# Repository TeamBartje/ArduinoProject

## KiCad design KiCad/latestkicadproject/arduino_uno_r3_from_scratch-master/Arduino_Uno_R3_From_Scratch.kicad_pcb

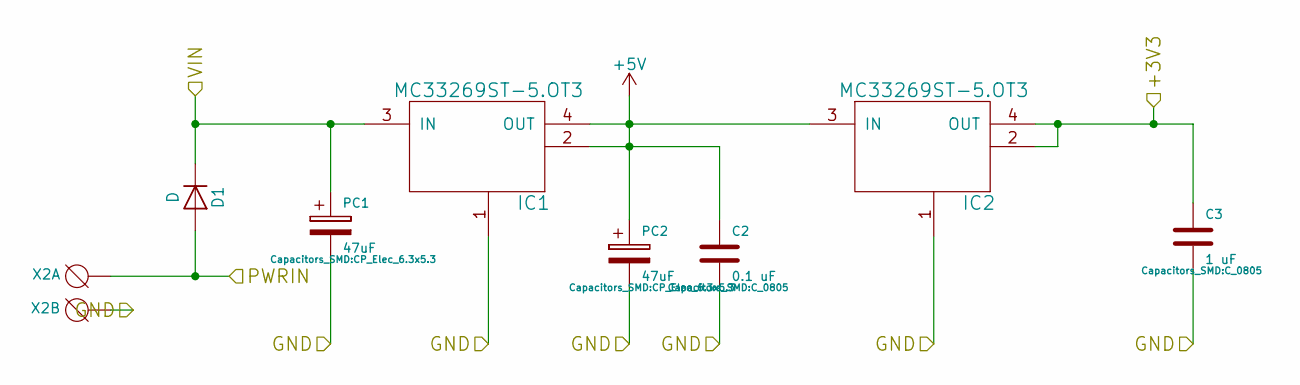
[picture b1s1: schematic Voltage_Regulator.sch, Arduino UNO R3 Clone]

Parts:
C2: 0.1 uF; C_0805
C3: 1 uF; C_0805
D1: D; D_MiniMELF_Handsoldering
IC1, IC2: MC33269ST-5.OT3; SOT230P700X175-4N
PC1, PC2: 47uF; CP_Elec_6.3x5.3
X2: DG3XX-02-3.5; degson-DG350-3.5-02P

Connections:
+5V: C2.1, IC1.2, IC1.4 (OUT), IC2.3 (IN), PC2.1; also elsewhere on the board
/Headers/+3V3: C3.1, IC2.2, IC2.4 (OUT); also elsewhere on the board
/Headers/VIN: D1.1 (K), IC1.3 (IN), PC1.1; also elsewhere on the board
/Motor Outputs/PWRIN: D1.2 (A), X2.1; also elsewhere on the board
GND: C2.2, C3.2, IC1.1, IC2.1, PC1.2, PC2.2, X2.2; also elsewhere on the board

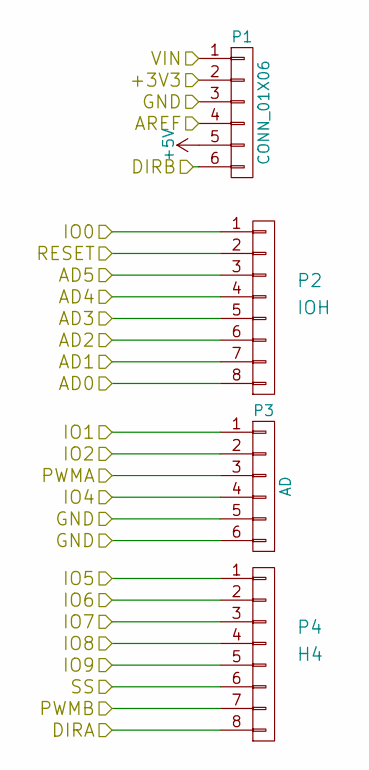
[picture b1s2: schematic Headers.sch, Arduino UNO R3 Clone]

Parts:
P1: CONN_01X06; Pin_Header_Straight_1x06_Pitch2.54mm
P2: IOH; Pin_Header_Straight_1x08_Pitch2.54mm
P3: AD; Pin_Header_Straight_1x06_Pitch2.54mm
P4: H4; Pin_Header_Straight_1x08_Pitch2.54mm

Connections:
+5V: P1.5; also elsewhere on the board
/ATMEGA328P/AD0: P2.8; also elsewhere on the board
/ATMEGA328P/AD1: P2.7; also elsewhere on the board
/ATMEGA328P/AD2: P2.6; also elsewhere on the board
/ATMEGA328P/AD3: P2.5; also elsewhere on the board
/ATMEGA328P/AD4: P2.4; also elsewhere on the board
/ATMEGA328P/AD5: P2.3; also elsewhere on the board
/ATMEGA328P/AREF: P1.4; also elsewhere on the board
/ATMEGA328P/DIRA: P4.8; also elsewhere on the board
/ATMEGA328P/DIRB: P1.6; also elsewhere on the board
/ATMEGA328P/IO0: P2.1; also elsewhere on the board
/ATMEGA328P/IO1: P3.1; also elsewhere on the board
/ATMEGA328P/IO2: P3.2; also elsewhere on the board
/ATMEGA328P/IO4: P3.4; also elsewhere on the board
/ATMEGA328P/IO5: P4.1; also elsewhere on the board
/ATMEGA328P/IO6: P4.2; also elsewhere on the board
/ATMEGA328P/IO7: P4.3; also elsewhere on the board
/ATMEGA328P/IO8: P4.4; also elsewhere on the board
/ATMEGA328P/IO9: P4.5; also elsewhere on the board
/ATMEGA328P/PWMA: P3.3; also elsewhere on the board
/ATMEGA328P/PWMB: P4.7; also elsewhere on the board
/ATMEGA328P/RESET: P2.2; also elsewhere on the board
/ATMEGA328P/SS: P4.6; also elsewhere on the board
/Headers/+3V3: P1.2; also elsewhere on the board
/Headers/VIN: P1.1; also elsewhere on the board
GND: P1.3, P3.5, P3.6; also elsewhere on the board

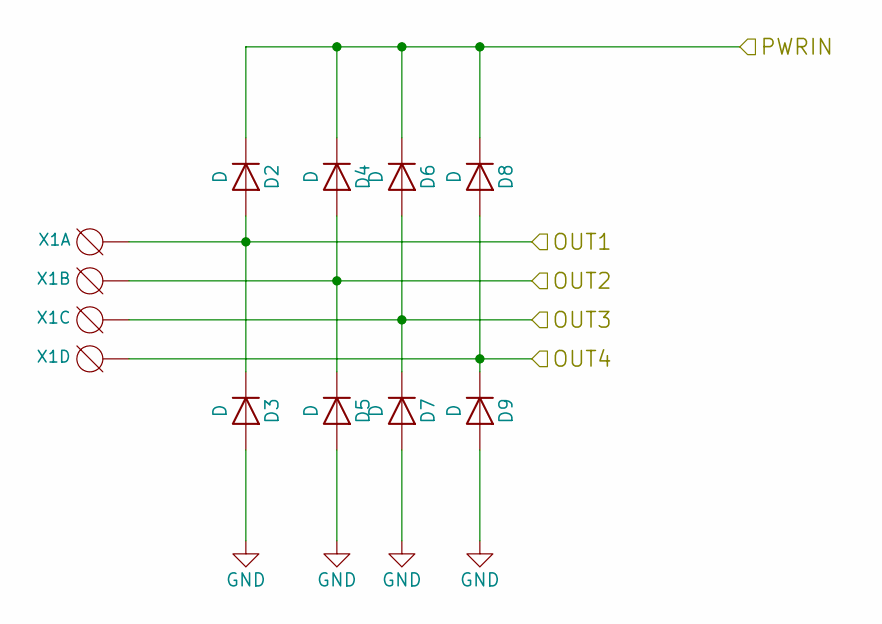
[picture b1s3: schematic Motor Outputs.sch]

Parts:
D2, D3, D4, D5, D6, D7, D8, D9: D; DIOM5437X240N
X1: DG3XX-04-3.5; degson-DG350-3.5-04P

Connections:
/Driver/OUT1: D2.2 (A), D3.1 (K), X1.1; also elsewhere on the board
/Driver/OUT2: D4.2 (A), D5.1 (K), X1.2; also elsewhere on the board
/Driver/OUT3: D6.2 (A), D7.1 (K), X1.3; also elsewhere on the board
/Driver/OUT4: D8.2 (A), D9.1 (K), X1.4; also elsewhere on the board
/Motor Outputs/PWRIN: D2.1 (K), D4.1 (K), D6.1 (K), D8.1 (K); also elsewhere on the board
GND: D3.2 (A), D5.2 (A), D7.2 (A), D9.2 (A); also elsewhere on the board

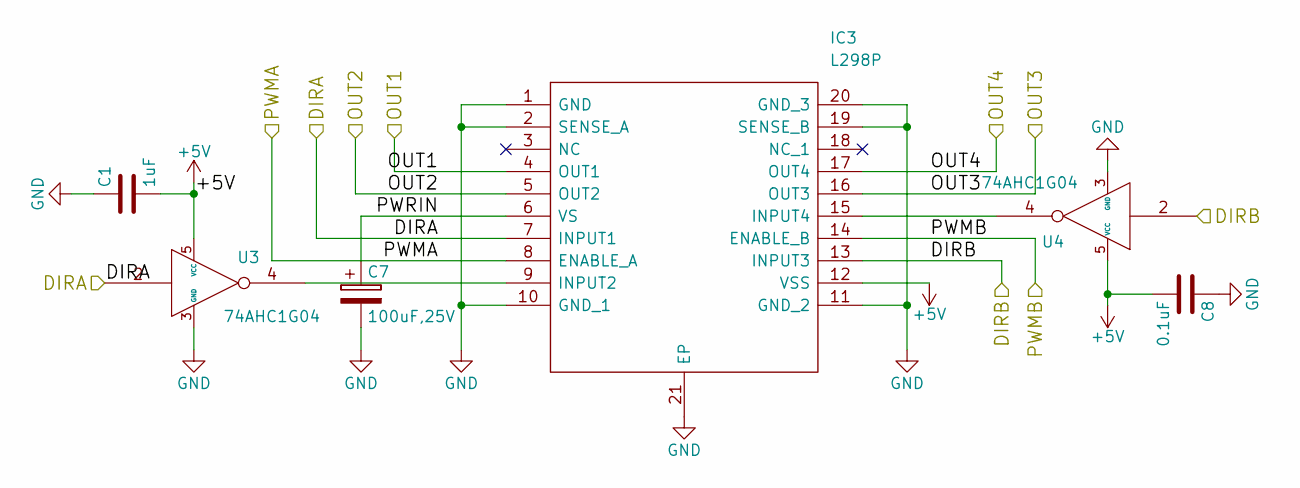
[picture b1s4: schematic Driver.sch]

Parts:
C1: 1uF; C_0805
C7: 100uF,25V; CP_Elec_6.3x5.3
C8: 0.1uF; C_0805
IC3: L298P; SOIC127P1420X360-21N; Manufacturer_Part_Number L298P
U3, U4: 74AHC1G04; 74AHC1G04GW

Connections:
+5V: C1.2, C8.2, IC3.12 (VSS), U3.5 (VCC), U4.5 (VCC); also elsewhere on the board
/ATMEGA328P/DIRA: IC3.7 (INPUT1), U3.2; also elsewhere on the board
/ATMEGA328P/DIRB: IC3.13 (INPUT3), U4.2; also elsewhere on the board
/ATMEGA328P/PWMA: IC3.8 (ENABLE_A); also elsewhere on the board
/ATMEGA328P/PWMB: IC3.14 (ENABLE_B); also elsewhere on the board
/Driver/OUT1: IC3.4 (OUT1); also elsewhere on the board
/Driver/OUT2: IC3.5 (OUT2); also elsewhere on the board
/Driver/OUT3: IC3.16 (OUT3); also elsewhere on the board
/Driver/OUT4: IC3.17 (OUT4); also elsewhere on the board
/Driver/PWRIN: C7.1, IC3.6 (VS)
GND: C1.1, C7.2, C8.1, IC3.1 (GND), IC3.2 (SENSE_A), IC3.10 (GND_1), IC3.11 (GND_2), IC3.19 (SENSE_B), IC3.20 (GND_3), IC3.21 (EP), U3.3 (GND), U4.3 (GND); also elsewhere on the board
unnamed: IC3.9 (INPUT2), U3.4
unnamed: IC3.15 (INPUT4), U4.4

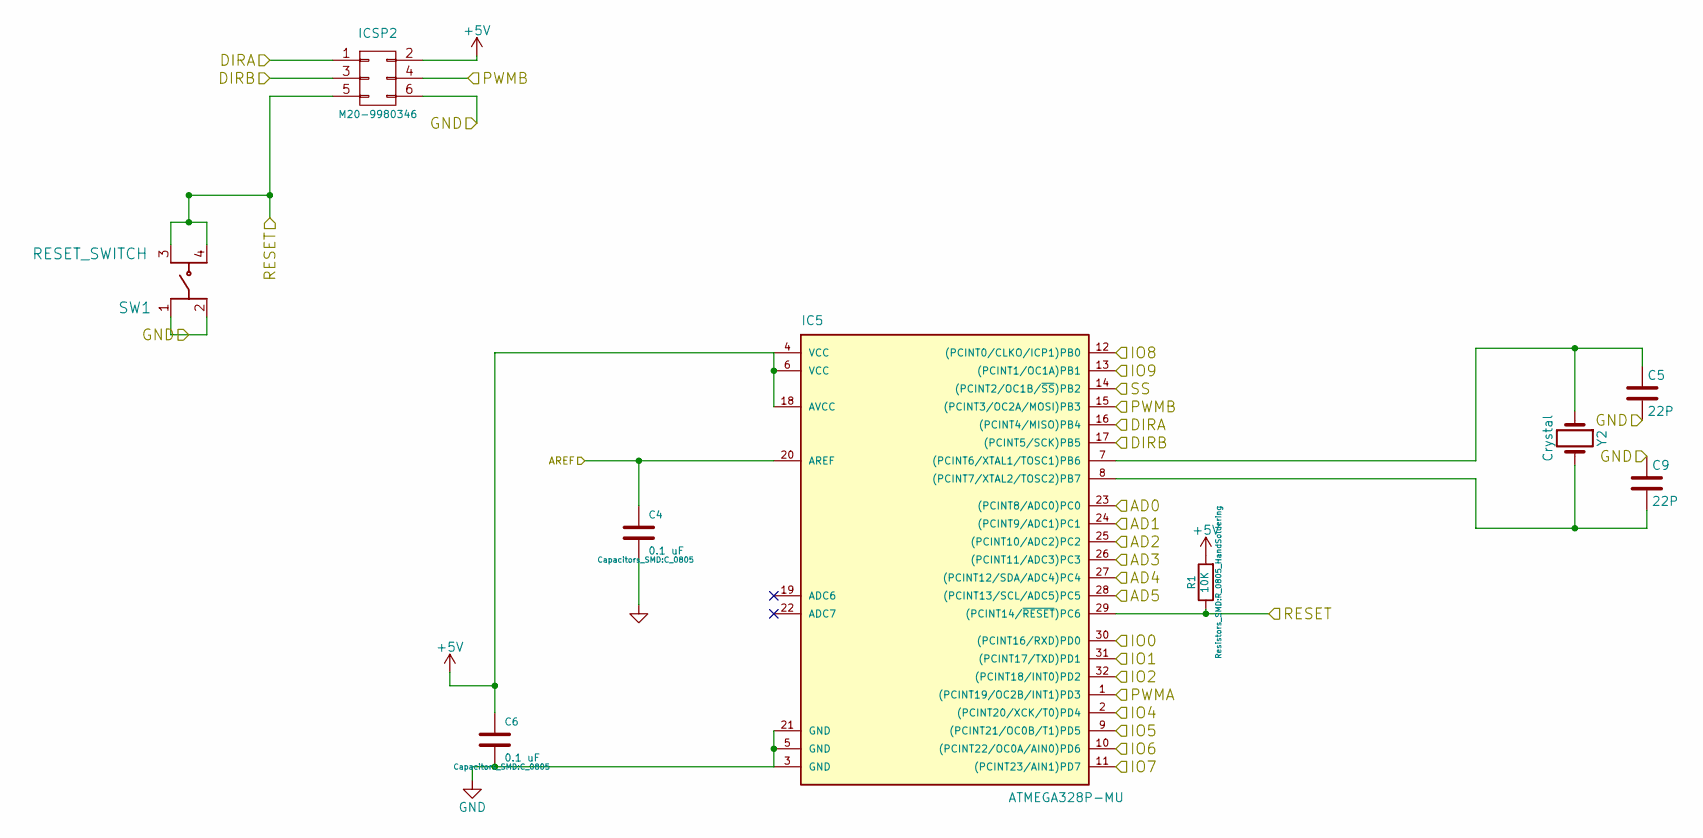
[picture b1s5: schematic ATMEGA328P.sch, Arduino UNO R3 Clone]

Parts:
C4, C6: 0.1 uF; C_0805
C5, C9: 22P; C_0805
IC5: ATMEGA328P-MU; QFP80P900X900X120-32N
ICSP2: M20-9980346; HDRV6W64P254_2X3_762X508X868P
R1: 10K; R_0805_HandSoldering
SW1: RESET_SWITCH; FSM4JSMATR
Y2: Crystal; HC%2f49US-(AT49)_1

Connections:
+5V: C6.1, IC5.4 (VCC), IC5.6 (VCC), IC5.18 (AVCC), ICSP2.2, R1.2; also elsewhere on the board
/ATMEGA328P/AD0: IC5.23 ((PCINT8/ADC0)PC0); also elsewhere on the board
/ATMEGA328P/AD1: IC5.24 ((PCINT9/ADC1)PC1); also elsewhere on the board
/ATMEGA328P/AD2: IC5.25 ((PCINT10/ADC2)PC2); also elsewhere on the board
/ATMEGA328P/AD3: IC5.26 ((PCINT11/ADC3)PC3); also elsewhere on the board
/ATMEGA328P/AD4: IC5.27 ((PCINT12/SDA/ADC4)PC4); also elsewhere on the board
/ATMEGA328P/AD5: IC5.28 ((PCINT13/SCL/ADC5)PC5); also elsewhere on the board
/ATMEGA328P/AREF: C4.1, IC5.20 (AREF); also elsewhere on the board
/ATMEGA328P/DIRA: IC5.16 ((PCINT4/MISO)PB4), ICSP2.1; also elsewhere on the board
/ATMEGA328P/DIRB: IC5.17 ((PCINT5/SCK)PB5), ICSP2.3; also elsewhere on the board
/ATMEGA328P/IO0: IC5.30 ((PCINT16/RXD)PD0); also elsewhere on the board
/ATMEGA328P/IO1: IC5.31 ((PCINT17/TXD)PD1); also elsewhere on the board
/ATMEGA328P/IO2: IC5.32 ((PCINT18/INT0)PD2); also elsewhere on the board
/ATMEGA328P/IO4: IC5.2 ((PCINT20/XCK/T0)PD4); also elsewhere on the board
/ATMEGA328P/IO5: IC5.9 ((PCINT21/OC0B/T1)PD5); also elsewhere on the board
/ATMEGA328P/IO6: IC5.10 ((PCINT22/OC0A/AIN0)PD6); also elsewhere on the board
/ATMEGA328P/IO7: IC5.11 ((PCINT23/AIN1)PD7); also elsewhere on the board
/ATMEGA328P/IO8: IC5.12 ((PCINT0/CLKO/ICP1)PB0); also elsewhere on the board
/ATMEGA328P/IO9: IC5.13 ((PCINT1/OC1A)PB1); also elsewhere on the board
/ATMEGA328P/PWMA: IC5.1 ((PCINT19/OC2B/INT1)PD3); also elsewhere on the board
/ATMEGA328P/PWMB: IC5.15 ((PCINT3/OC2A/MOSI)PB3), ICSP2.4; also elsewhere on the board
/ATMEGA328P/RESET: IC5.29 ((PCINT14/~RESET~)PC6), ICSP2.5, R1.1, SW1.3, SW1.4; also elsewhere on the board
/ATMEGA328P/SS: IC5.14 ((PCINT2/OC1B/~SS~)PB2); also elsewhere on the board
GND: C4.2, C5.2, C6.2, C9.1, IC5.3 (GND), IC5.5 (GND), IC5.21 (GND), ICSP2.6, SW1.1, SW1.2; also elsewhere on the board
unnamed: C5.1, IC5.7 ((PCINT6/XTAL1/TOSC1)PB6), Y2.1
unnamed: C9.2, IC5.8 ((PCINT7/XTAL2/TOSC2)PB7), Y2.2

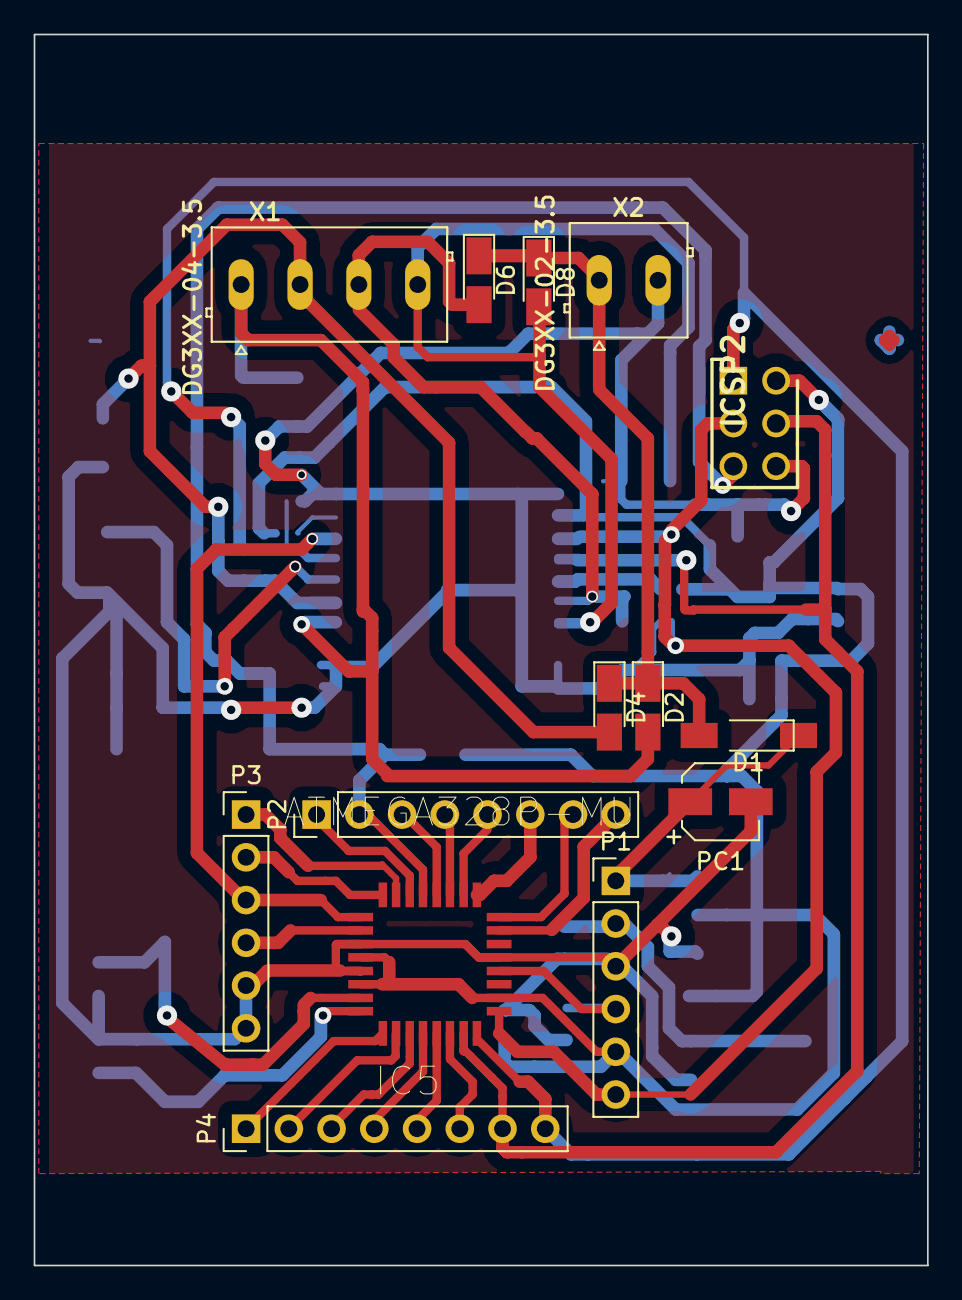
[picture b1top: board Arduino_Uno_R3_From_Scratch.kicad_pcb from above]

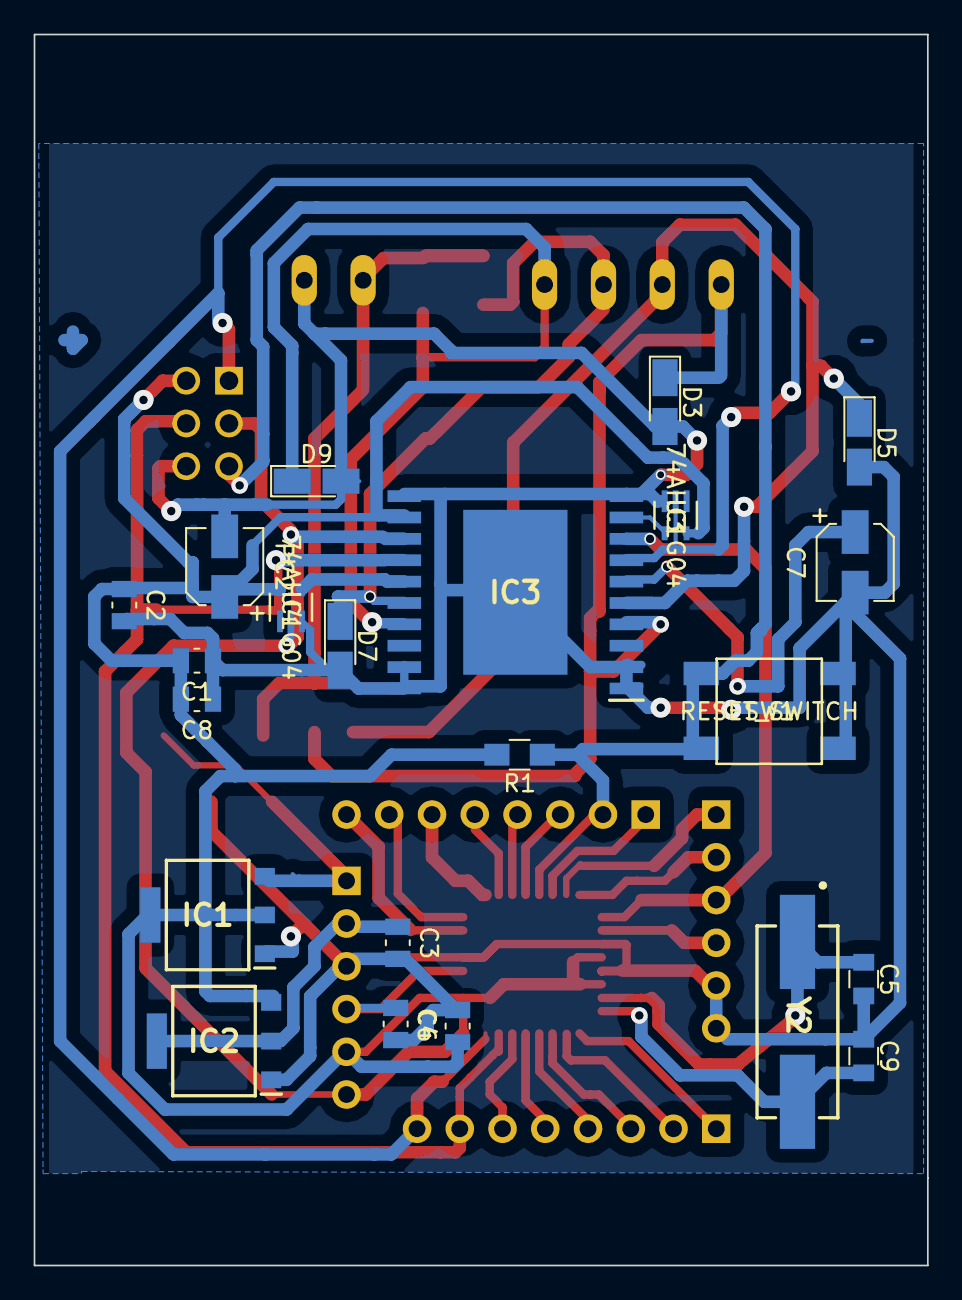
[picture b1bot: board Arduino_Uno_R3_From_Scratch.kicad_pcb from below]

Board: 2 copper layers, 53.1 x 73.2 mm, 36 parts (22 on the bottom side), 36 nets.

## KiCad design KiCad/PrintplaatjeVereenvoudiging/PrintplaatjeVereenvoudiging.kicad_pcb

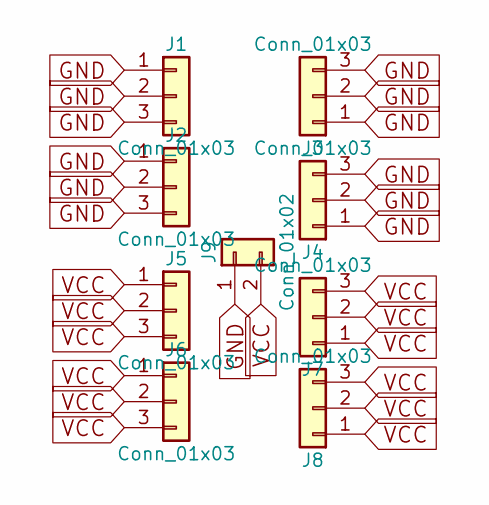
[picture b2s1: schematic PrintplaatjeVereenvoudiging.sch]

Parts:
J1, J2, J3, J4, J5, J6, J7, J8: Conn_01x03; Pin_Header_Angled_1x03_Pitch2.54mm
J9: Conn_01x02; Pin_Header_Angled_1x02_Pitch2.54mm

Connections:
GND: J1.1, J1.2, J1.3, J2.1, J2.2, J2.3, J3.1, J3.2, J3.3, J4.1, J4.2, J4.3, J9.1
VCC: J5.1, J5.2, J5.3, J6.1, J6.2, J6.3, J7.1, J7.2, J7.3, J8.1, J8.2, J8.3, J9.2

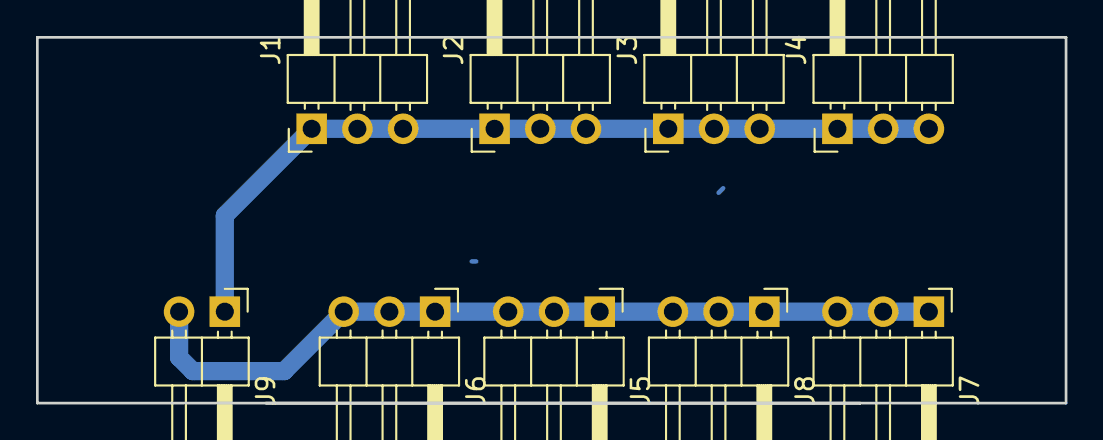
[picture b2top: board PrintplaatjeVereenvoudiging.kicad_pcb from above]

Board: 2 copper layers, 57.1 x 20.3 mm, 9 parts (0 on the bottom side), 2 nets.

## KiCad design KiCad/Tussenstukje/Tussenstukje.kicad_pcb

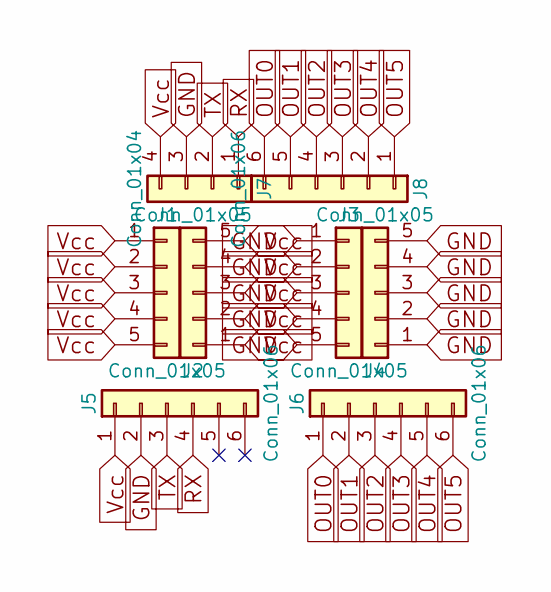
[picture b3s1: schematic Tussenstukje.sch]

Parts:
J1, J2, J3, J4: Conn_01x05; Pin_Header_Straight_1x05_Pitch2.54mm
J5, J6: Conn_01x06; Pin_Header_Straight_1x06_Pitch2.54mm
J7: Conn_01x04; Pin_Header_Angled_1x04_Pitch2.54mm
J8: Conn_01x06; Pin_Header_Angled_1x06_Pitch2.54mm

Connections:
GND: J3.1, J3.2, J3.3, J3.4, J3.5, J4.1, J4.2, J4.3, J4.4, J4.5, J5.2, J7.3
OUT0: J6.1, J8.6
OUT1: J6.2, J8.5
OUT2: J6.3, J8.4
OUT3: J6.4, J8.3
OUT4: J6.5, J8.2
OUT5: J6.6, J8.1
RX: J5.4, J7.1
TX: J5.3, J7.2
Vcc: J1.1, J1.2, J1.3, J1.4, J1.5, J2.1, J2.2, J2.3, J2.4, J2.5, J5.1, J7.4

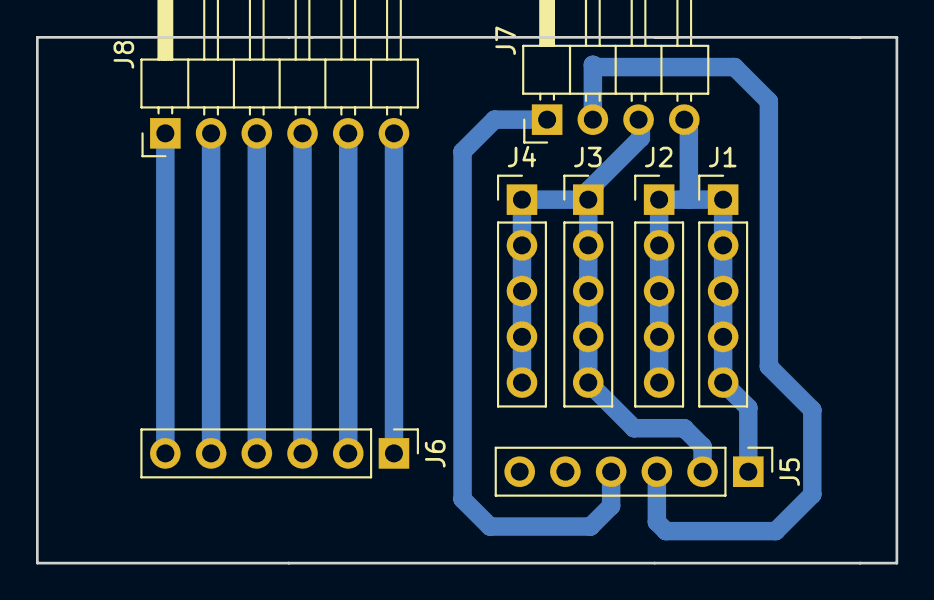
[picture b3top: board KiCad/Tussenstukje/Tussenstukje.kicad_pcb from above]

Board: 2 copper layers, 47.8 x 29.2 mm, 8 parts (0 on the bottom side), 10 nets.

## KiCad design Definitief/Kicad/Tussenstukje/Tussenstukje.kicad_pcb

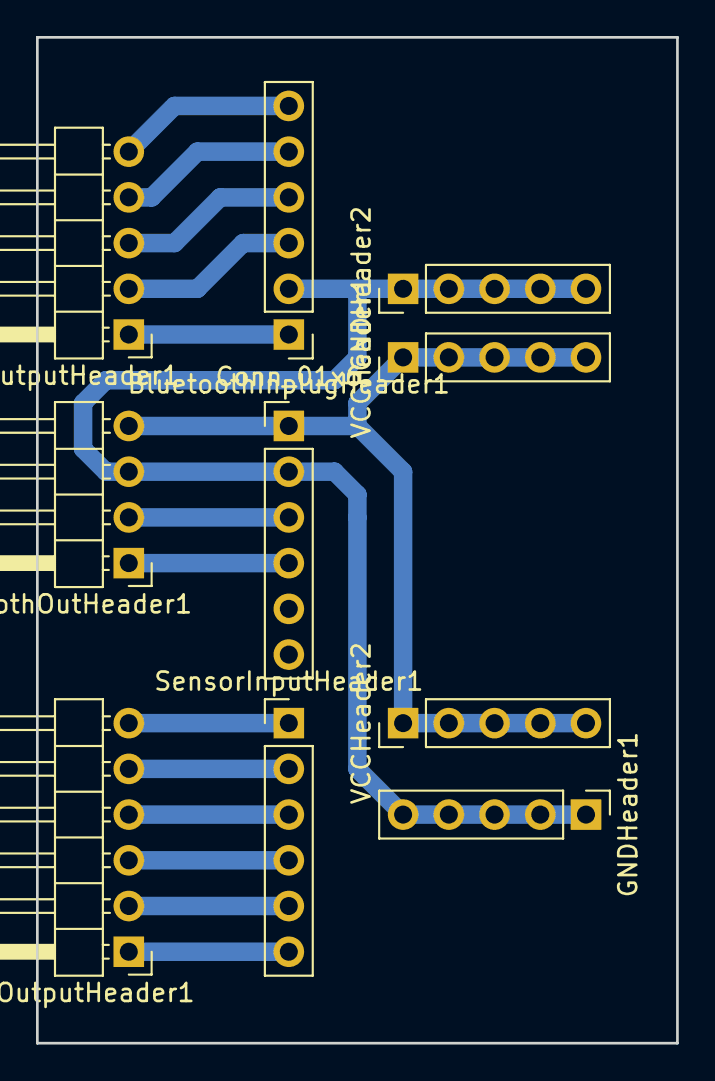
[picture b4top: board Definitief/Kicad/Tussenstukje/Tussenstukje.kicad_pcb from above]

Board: 2 copper layers, 35.6 x 55.9 mm, 10 parts (0 on the bottom side), 15 nets.

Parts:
BluetoothInplugHeader1: Conn_01x06; Pin_Header_Straight_1x06_Pitch2.54mm
BluetoothOutHeader1: BluetoothOutputHeader; Pin_Header_Angled_1x04_Pitch2.54mm
Conn_01x6: RFIDInplugHeader; Pin_Header_Straight_1x06_Pitch2.54mm
GNDHeader1: GNDHeader1; Pin_Header_Straight_1x05_Pitch2.54mm
GNDHeader2: GNDHeader2; Pin_Header_Straight_1x05_Pitch2.54mm
RFIDOutputHeader1: Conn_01x05; Pin_Header_Angled_1x05_Pitch2.54mm
SensorInputHeader1: SensorInputHeader; Pin_Header_Straight_1x06_Pitch2.54mm
SensorOutputHeader1: Conn_01x06; Pin_Header_Angled_1x06_Pitch2.54mm
VCCHeader1, VCCHeader2: Conn_01x05; Pin_Header_Straight_1x05_Pitch2.54mm

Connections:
GND: BluetoothInplugHeader1.2, BluetoothOutHeader1.3, Conn_01x6.2, GNDHeader1.1, GNDHeader1.2, GNDHeader1.3, GNDHeader1.4, GNDHeader1.5, GNDHeader2.1, GNDHeader2.2, GNDHeader2.3, GNDHeader2.4, GNDHeader2.5
MISO: Conn_01x6.3, RFIDOutputHeader1.2
MOSI: Conn_01x6.4, RFIDOutputHeader1.3
OUT0: SensorInputHeader1.6, SensorOutputHeader1.1
OUT1: SensorInputHeader1.5, SensorOutputHeader1.2
OUT2: SensorInputHeader1.4, SensorOutputHeader1.3
OUT3: SensorInputHeader1.3, SensorOutputHeader1.4
OUT4: SensorInputHeader1.2, SensorOutputHeader1.5
OUT5: SensorInputHeader1.1, SensorOutputHeader1.6
RX: BluetoothInplugHeader1.4, BluetoothOutHeader1.1
SCK: Conn_01x6.5, RFIDOutputHeader1.4
SDA: Conn_01x6.6, RFIDOutputHeader1.5
TX: BluetoothInplugHeader1.3, BluetoothOutHeader1.2
VCC3.3: Conn_01x6.1, RFIDOutputHeader1.1
Vcc: BluetoothInplugHeader1.1, BluetoothOutHeader1.4, VCCHeader1.1, VCCHeader1.2, VCCHeader1.3, VCCHeader1.4, VCCHeader1.5, VCCHeader2.1, VCCHeader2.2, VCCHeader2.3, VCCHeader2.4, VCCHeader2.5

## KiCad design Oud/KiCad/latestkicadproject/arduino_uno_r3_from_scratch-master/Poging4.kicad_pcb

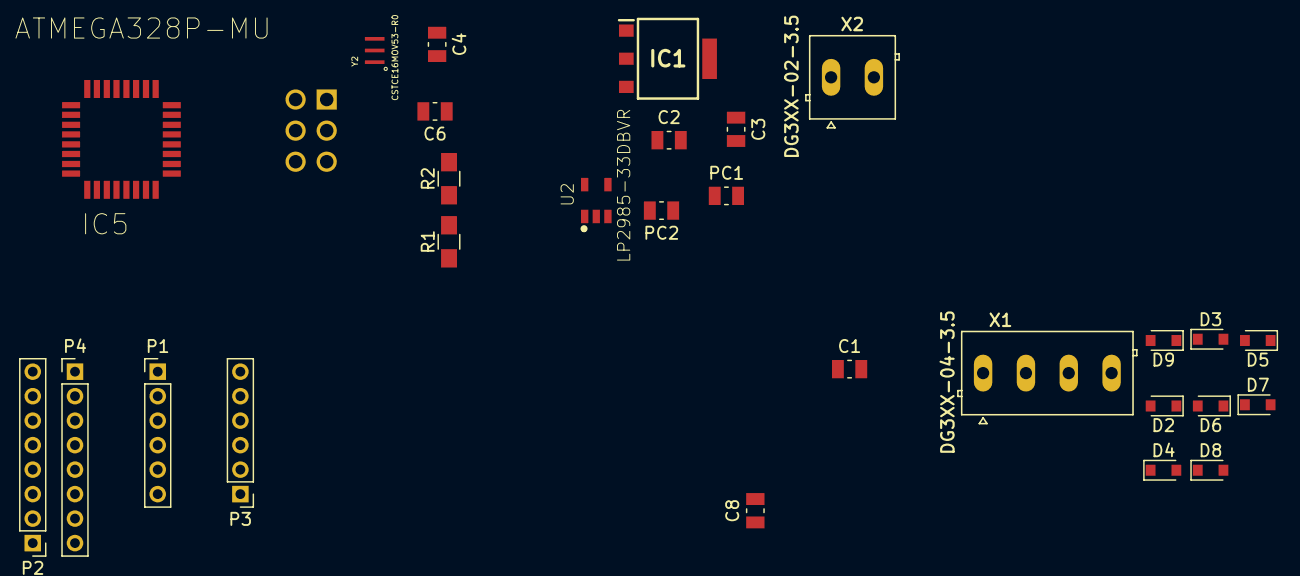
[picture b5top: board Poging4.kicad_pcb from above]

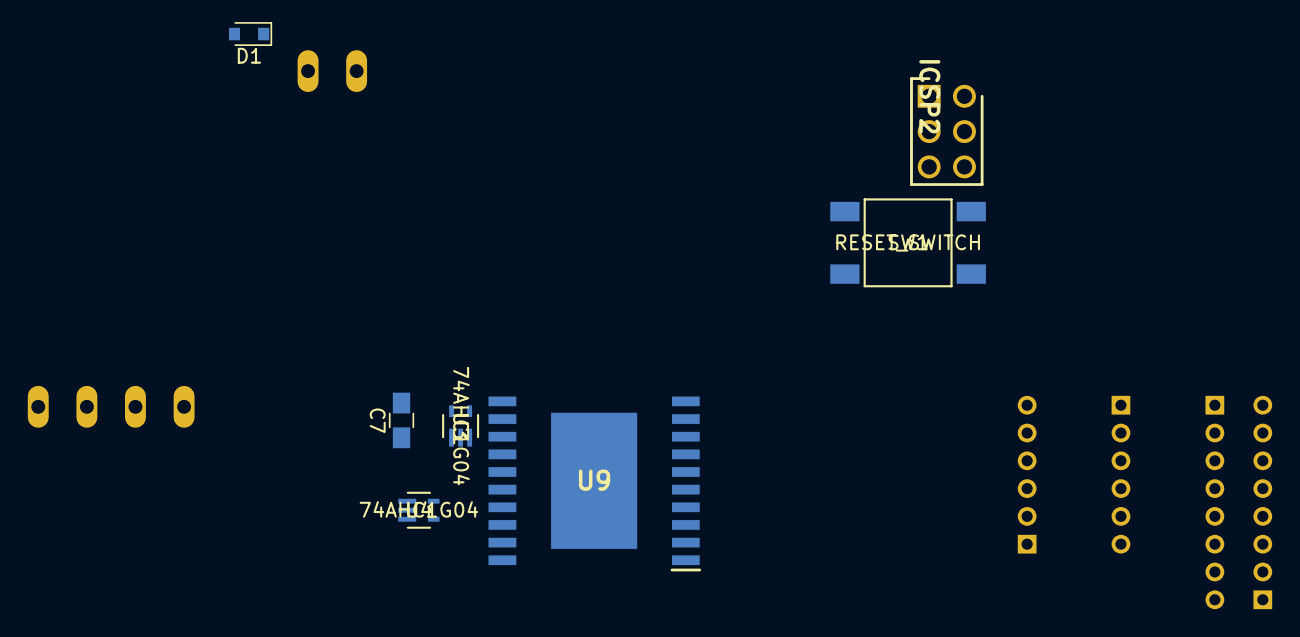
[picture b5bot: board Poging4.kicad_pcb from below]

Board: 2 copper layers, 35 parts (7 on the bottom side), 37 nets, no tracks yet.

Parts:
C1: 1uF; C_0805_2012Metric
C2, C4, C6: 0.1 uF; C_0805_2012Metric
C3: 1 uF; C_0805_2012Metric
C7: 100uF,25V; C_0805_HandSoldering
C8: 0.1uF; C_0805_2012Metric
D1, D2, D3, D4, D5, D6, D7, D8, D9: D; D_0805
IC1: MC33269ST-5.OT3; SOT230P700X175-4N
IC5: ATMEGA328P-MU; QFP80P900X900X120-32N
ICSP2: M20-9980346; HDRV6W64P254_2X3_762X508X868P
P1: CONN_01X06; Pin_Header_Straight_1x06_Pitch2.00mm
P2: IOH; Pin_Header_Straight_1x08_Pitch2.00mm
P3: AD; Pin_Header_Straight_1x06_Pitch2.00mm
P4: IOL; Pin_Header_Straight_1x08_Pitch2.00mm
PC1, PC2: 47uF; C_0805_2012Metric
R1: 10K; R_0805_HandSoldering
R2: 1M; R_0805_HandSoldering
SW1: RESET_SWITCH; FSM4JSMATR
U2: LP2985-33DBVR; SOT95P280X145-5N
U3, U4: 74AHC1G04; 74AHC1G04GW
U9: L298; SOIC127P1420X360-21N
X1: DG3XX-04-3.5; degson-DG350-3.5-04P
X2: DG3XX-02-3.5; degson-DG350-3.5-02P
Y2: CSTCE16MOV53-R0; OSC_CSTCE16M0V53-R0

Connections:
+5V: C1.2, C2.1, C6.1, C8.2, IC1.2, IC1.4, IC5.4, IC5.6, IC5.18, ICSP2.2, P1.3, PC2.1, R1.2, U2.1, U2.3, U3.5, U4.5, U9.12
/ATMEGA328P/AD0: IC5.23, P3.1
/ATMEGA328P/AD1: IC5.24, P3.2
/ATMEGA328P/AD2: IC5.25, P3.3
/ATMEGA328P/AD3: IC5.26, P3.4
/ATMEGA328P/AD4: IC5.27, P3.5
/ATMEGA328P/AD5: IC5.28, P3.6
/ATMEGA328P/AREF: C4.1, IC5.20, P2.8
/ATMEGA328P/DIRA: IC5.16, ICSP2.1, P2.5, U3.2, U9.7
/ATMEGA328P/DIRB: IC5.17, ICSP2.3, P2.6, U4.2, U9.13
/ATMEGA328P/IO0: IC5.30, P4.1
/ATMEGA328P/IO1: IC5.31, P4.2
/ATMEGA328P/IO2: IC5.32, P4.3
/ATMEGA328P/IO4: IC5.2, P4.5
/ATMEGA328P/IO5: IC5.9, P4.6
/ATMEGA328P/IO6: IC5.10, P4.7
/ATMEGA328P/IO7: IC5.11, P4.8
/ATMEGA328P/IO8: IC5.12, P2.1
/ATMEGA328P/IO9: IC5.13, P2.2
/ATMEGA328P/PWMA: IC5.1, P4.4, U9.8
/ATMEGA328P/PWMB: IC5.15, ICSP2.4, P2.4, U9.14
/ATMEGA328P/RESET: IC5.29, ICSP2.5, P1.1, R1.1, SW1.3, SW1.4
/ATMEGA328P/SS: IC5.14, P2.3
/Driver/OUT1: D2.2, D3.1, U9.4, X1.1
/Driver/OUT2: D4.2, D5.1, U9.5, X1.2
/Driver/OUT3: D6.2, D7.1, U9.16, X1.3
/Driver/OUT4: D8.2, D9.1, U9.17, X1.4
/Driver/PWRIN: C7.1, U9.6
/Headers/+3V3: C3.1, P1.2, U2.5
/Headers/VIN: D1.1, IC1.3, P1.6, PC1.1
/Motor Outputs/PWRIN: D1.2, D2.1, D4.1, D6.1, D8.1, X2.1
GND: C1.1, C3.2, C6.2, C7.2, C8.1, D3.2, D5.2, D7.2, D9.2, IC5.3, IC5.5, IC5.21, ICSP2.6, P1.4, P1.5, P2.7, U2.2, U3.3, U4.3, U9.1, U9.2, U9.10, U9.11, U9.19, U9.20
unnamed: IC5.7, R2.2, Y2.3
unnamed: IC5.8, R2.1, Y2.1
unnamed: SW1.1, SW1.2
unnamed: U3.4, U9.9
unnamed: U4.4, U9.15

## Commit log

2017-11-08 ToevoegenVanBestanden
2017-11-09 voorbeeldLib
2017-11-09 CodeFunctiesMotor
    Functies vooruit, gewoonRechts, gewoonLinks, scherpRechts en scherpLinks
2017-11-09 ToevoegenAchteruit
    Functie achteruit toegevoegd
2017-11-09 ArduinoOntwerp
    Motor Outputs zijn nog niet helemaal klaar.
2017-11-10 Bluetooth getest
2017-11-13 Bluetooth Communicatie geïntroduceerd.
    Bluetoothcommunicatie is in beide richtingen mogelijk
2017-11-14 Update Printplaat
2017-11-23 Blue library
2018-02-14 14feb
2018-02-14 TestenSensor
    Testen van de lijndetector
2018-02-14 14feb1
2018-02-21 21feb
2018-02-21 21 feb
2018-02-21 KiCad
    Nieuwe versie met Globale labels
2018-02-27 27feb
2018-02-28 28feb
2018-02-28 28feb
    Aanpassing KiCad+deel footprints
2018-03-05 Toevoegen footprints Kicad
2018-03-07 Aanpassing KiCad PCB ontwerp + footprints
2018-03-19 pcb routing
2018-03-21 PCB routing v1
2018-03-22 correctie gnd-fouten
2018-03-24 verbeteringen kicad
2018-04-04 up to date brengen van nieuwe laptop
2018-04-04 toevoegen van oude versies
2018-04-04 verbetering code
2018-04-19 Herschikking Github
2018-04-19 Herschikking 2
2018-04-19 PCBtotaal
2018-04-19 herschikking 3
2018-04-19 herschikking4
2018-04-19 herschikking5
2018-04-19 Verslag
2018-04-19 Vormgeving Verslag
2018-04-24 Verslag (HW,Coach en Opdracht)
2018-04-24 24042018
2018-04-24 Toevoegen onkosten
2018-04-24 psuh
2018-04-24 VerslagVerandering
2018-04-25 verder werken aan verslag
2018-04-25 Toevoegen foto's
2018-04-25 Toevoegen laatste delen tekst, afbeeldingen volgen nog
2018-04-25 Afwerken tekst
2018-04-26 verderwerken verslag
2018-04-26 verderwerken
2018-04-26 Afwerken verslag
2018-04-27 Laatste kleine foutjes uit gehaald
2018-04-27 laatste veranderingen
2018-05-02 laatste
2018-05-03 Final push arduinoproject

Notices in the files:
parts and their libraries:
Copyright 2016 Accelerated Designs. All rights reserved.
